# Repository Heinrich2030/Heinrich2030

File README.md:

# Steuer-Rechner

Eigene Web-App zur Schätzung der Einkommensteuer in Deutschland – jahresunabhängig,
läuft komplett im Browser (keine Datenübertragung), mit KI-gestützter Aktualisierung
der Steuerwerte.

## Funktionen
- Einkommensteuer nach § 32a EStG, Grund- und Splittingtarif
- Solidaritätszuschlag (Freigrenze, Milderungszone), Kirchensteuer 8 %/9 %
- Anlage N für 1–2 Personen: Entfernungspauschale, Homeoffice, Arbeitsmittel,
  Arbeitnehmer-Pauschbetrag, Renten- und Basis-Kranken-/Pflegeversicherung
- Kinder: Günstigerprüfung Kindergeld/Kinderfreibetrag, Entlastungsbetrag Alleinerziehende
- Spenden, haushaltsnahe Dienstleistungen und Handwerkerleistungen (§ 35a)
- Anlage KAP: Abgeltungsteuer mit Sparerpauschbetrag
- Erstattung/Nachzahlung im Vergleich zu einbehaltenen Steuern
- Steuerwerte für 2023–2026 (2026 vorläufig); unbekannte Jahre nutzen das neueste Jahr mit Warnhinweis

## Starten
```bash
npm start      # http://localhost:8080
npm test
```
Ohne Build-Schritt – die Dateien können auch direkt auf GitHub Pages oder jedem Webspace liegen.

## Jahresunabhängigkeit & KI-Überwachung
Alle Jahreswerte stehen in `src/data/tax-years.js`, die Rechenlogik in `src/engine/tax.js`
ist jahresneutral. Wie neue Jahre automatisch nachgetragen werden: [docs/KI-UEBERWACHUNG.md](docs/KI-UEBERWACHUNG.md).

## Noch nicht enthalten
Außergewöhnliche Belastungen, Selbständigkeit/Gewerbe, Vermietung, Höchstbeträge der
Vorsorgeaufwendungen, Progressionsvorbehalt, ELSTER-Übermittlung (ERiC).

> Schätzung ohne Gewähr – keine Steuerberatung.

## Spartipps
Die App analysiert deine Eingaben und zeigt Spartipps, sortiert nach Ersparnis in Euro.
Jeder Betrag ist eine echte Vergleichsrechnung mit der Engine („Was wäre, wenn …“), z. B.
Homeoffice-Tage, Handwerkerkosten, Basisrente, Spenden, Splitting-Vorteil, Günstigerprüfung
und Freistellungsauftrag bei Kapitalerträgen. Logik: `src/engine/tipps.js`.

## Weitere Projekte

- [Kabeltester](kabeltester/README.md) – Tischgerät mit 7″-Touchdisplay, 128–256 Testpunkten und 4-Leiter-Widerstandsmessung.

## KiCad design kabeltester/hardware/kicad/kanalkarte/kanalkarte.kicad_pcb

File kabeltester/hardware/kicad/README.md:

# KiCad-Projekte des Kabeltesters

Drei Platinen, erzeugt mit KiCad 7 aus einer gemeinsamen Netzliste (Python-Generator).

| Projekt | Größe | Lagen | Bauteile | Inhalt |
|---|---|---|---|---|
| [`kanalkarte/`](kanalkarte) | 118 × 74 mm | 4 | 413 | 64 Testpunkte, 8× ADG1606, 8× CD74HCT4067, Schutzbeschaltung, DIN-41612-Federleiste. Wird **zweimal** gebaut (Seite A und B). |
| [`messkarte/`](messkarte) | 120 × 90 mm | 4 | 112 | Pico 2, ADS1220, REF5025, Stromsenke, Moduswahl, USB-C, Anschlüsse für Display/Taster/LEDs |
| [`adapter_rj45/`](adapter_rj45) | 100 × 60 mm | 2 | 7 | Vorlage für Steckeradapter: 2× RJ45 + EEPROM, DIN-41612-Messerleiste |

Jedes Projekt enthält Schaltplan (`.kicad_sch`, bei der Kanalkarte mit vier Unterblättern),
Leiterplatte (`.kicad_pcb`), DRC-Bericht und im Ordner `fertigung/`:

- `*-gerber.zip` – Gerber + Bohrdaten (für JLCPCB, Aisler, Multi-CB …)
- `*-bom-jlcpcb.csv` – Stückliste, gruppiert, mit Hersteller-Nummer und (wo bekannt) LCSC-Nummer
- `*-cpl-jlcpcb.csv` – Bestückungsliste (Position, Seite, Drehung)
- `*.step.zip` – 3D-Modell der bestückten Platine

Gehäuse und Gesamtbaugruppe als STEP liegen in [`../../gehaeuse/step/`](../../gehaeuse/step).

## Stand

| Schritt | Status |
|---|---|
| Schaltpläne | fertig; KiCads eigene Netzliste stimmt mit dem Modell überein (automatisch geprüft) |
| Bauteilplatzierung | fertig; keine Überlappungen, Befestigungslöcher passen zu den Gehäusedomen |
| Lagenaufbau | Messkarte 4 Lagen (In1 GND, In2 Signal), Kanalkarte 6 Lagen (In1 GND, In2–In4 Signal), Adapter 2 Lagen; GND-Flächen auf den Außenlagen, 5VA als 0,4-mm-Leiterbahn |
| 3D-Kollisionsprüfung | Platinen, Display, Gehäuse und Boden überschneiden sich nicht |
| **Leiterbahnen** | **offen** – Kanalkarte 944, Messkarte 294, Adapter 21 Verbindungen (siehe unten) |
| Gerber | erzeugt, aber **erst nach dem Routen bestellbar** |

## Vor der Bestellung – Pflichtpunkte

1. **Leiterbahnen ziehen** (Autorouter oder von Hand), dann DRC ohne Fehler.
2. **Pinbelegungen prüfen**, die nicht aus der KiCad-Bibliothek stammen
   (Symbole in `bibliothek/kabeltester.kicad_sym`):
   - ADG1606 (TSSOP-28) – teilweise per Websuche bestätigt (VDD = 1, S16 = 4, S8 = 26, VSS = 27, D = 28),
     der Rest folgt der Pinbelegung der Familie ADG406/1206. Mit dem Datenblatt von Analog Devices abgleichen.
   - BAV199 (SOT-23: 1 = Anode D1, 2 = Kathode D2, 3 = Mitte)
   - PESD2CAN (SOT-23: 1/2 = Leitungen, 3 = gemeinsam)
   - Raspberry Pi Pico 2 (Pinbelegung wie Pico 1)
3. **DIN-41612-Ausrichtung** am ersten Muster prüfen: Messerleiste des Adapters und Federleiste der
   Kanalkarte haben Pin a1 jeweils rechts (von vorne gesehen). Ob Reihe a vorne oder hinten liegt,
   hängt vom Steckverbinder-Hersteller ab – im Zweifel die Federleiste in `layouts.py` um 180° drehen.
4. **LCSC-Nummern** ergänzen: Nur gängige Teile und der ADG1606 (C208204) sind eingetragen. Fehlende
   Nummern im JLCPCB-Teilekatalog zuordnen oder die Teile von Mouser/DigiKey selbst bestücken.
5. Die USB-C-Buchse (Footprint `GCT_USB4105`) hat laut DRC 0,19 mm zwischen Befestigungsloch und Pad
   (Regel 0,25 mm). Das steckt im Standard-Footprint und ist bei JLCPCB fertigbar.

## Leiterbahnen ziehen (Autorouter Freerouting)

In KiCad: *Plugin- und Inhaltsverwaltung* → „Freerouting“ installieren → im Leiterplatten-Editor
*Werkzeuge → Externe Plugins → Freerouting*. Danach *Flächen füllen* (Taste `B`) und *DRC*.

Oder automatisch über den Generator (Java 17+, `Xvfb`, `xdotool` und die Datei `freerouting-1.9.0.jar` von
github.com/freerouting/freerouting nötig):

```bash
FREEROUTING_JAR=/pfad/zu/freerouting-1.9.0.jar python3.12 generator/bauen.py --routen
```

Die Kanalkarte ist sehr dicht (413 Bauteile). Mit 4 Lagen blieben nach dem Autorouter rund 290
Verbindungen offen, deshalb hat sie 6 Lagen. Das Routing läuft in Runden (`generator/routen.py`),
nach jeder Runde wird gespeichert.

## Neu erzeugen

Alles entsteht aus `generator/` – Änderungen dort machen, nicht in den KiCad-Dateien (sie werden
überschrieben). Voraussetzung: KiCad 7 mit Python-Modul `pcbnew` (Linux: Paket `kicad`, dazu
`kicad-symbols`, `kicad-footprints`, `kicad-packages3d`).

```bash
cd kabeltester/hardware/kicad
python3.12 generator/bauen.py              # Schaltpläne, Leiterplatten, Fertigungsdaten
python3.12 generator/bauen.py --nur-schaltplan
```

| Datei | Aufgabe |
|---|---|
| `generator/platinen.py` | Netzlisten aller Platinen (Bauteile, Werte, Footprints, Netze) |
| `generator/layouts.py` | Platzierung und Mechanik (Maße, Lochpositionen) |
| `generator/schaltplan.py` | schreibt die `.kicad_sch`-Dateien |
| `generator/leiterplatte.py` | baut die `.kicad_pcb`, Flächen, DRC, Fertigungsdaten |
| `generator/netzvergleich.py` | vergleicht KiCads Netzliste mit dem Modell |
| `generator/eigene_bibliothek.py` | eigene Symbole und den Pico-2-Footprint |

## Gehäuse als STEP

```bash
pip install cadquery
python ../../gehaeuse/gehaeuse_step.py
```

Erzeugt `gehaeuse_oberschale.step/.stl`, `gehaeuse_boden.step/.stl` und die Gesamtbaugruppe
`kabeltester_baugruppe.step.zip` (gezippt ca. 40 MB, entpackt ca. 290 MB). STEP lässt sich in
SolidWorks, Fusion 360, FreeCAD, Onshape und den meisten anderen CAD-Programmen öffnen.

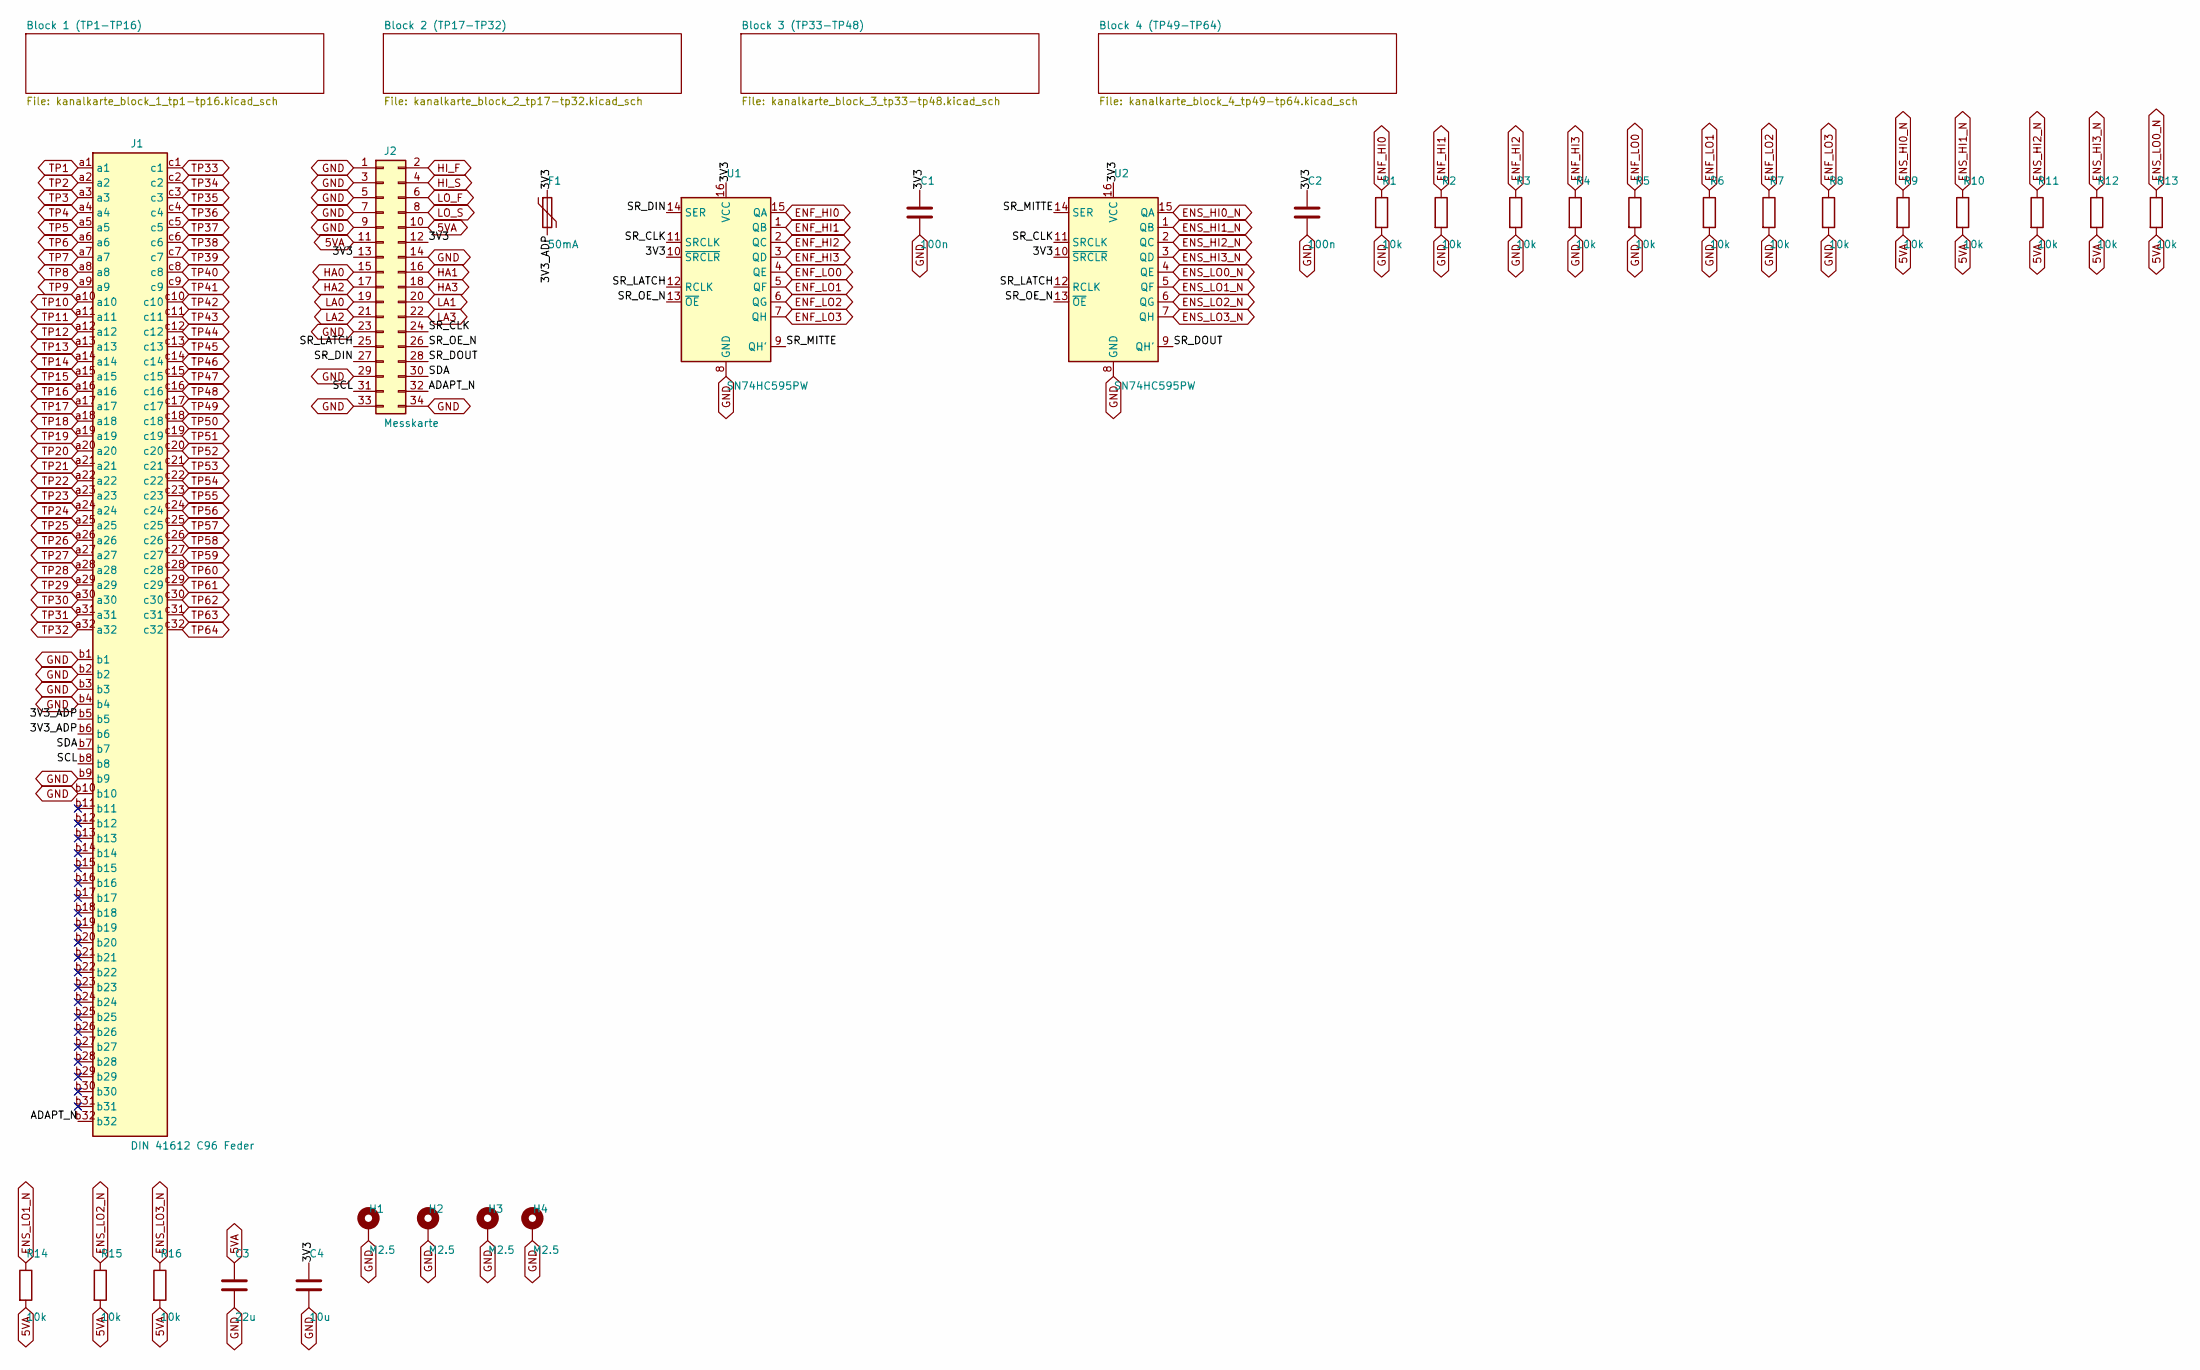
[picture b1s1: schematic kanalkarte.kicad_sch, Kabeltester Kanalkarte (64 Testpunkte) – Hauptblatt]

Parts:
C1, C2: 100n; C_0603_1608Metric; LCSC C14663
C3: 22u; C_1206_3216Metric
C4: 10u; C_0805_2012Metric; LCSC C15850
F1: 50mA; Fuse_0805_2012Metric; MPN Bourns MF-PSMF005X-2
H1, H2, H3, H4: M2.5; MountingHole_2.7mm_M2.5_Pad_Via
J1: DIN 41612 C96 Feder; DIN41612_C_3x32_Female_Vertical_THT; MPN Harting DIN-Signal C096 F gerade
J2: Messkarte; IDC-Header_2x17_P2.54mm_Vertical; MPN Wannenstecker 2x17
R1, R2, R3, R4, R5, R6, R7, R8, R9, R10, R11, R12, R13, R14, R15, R16: 10k; R_0603_1608Metric; LCSC C25804
U1, U2: SN74HC595PW; TSSOP-16_4.4x5mm_P0.65mm; LCSC C5947

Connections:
3V3: C1.1, C2.1, C4.1, F1.1, J2.12, J2.13, U1.10 (~SRCLR), U1.16 (VCC), U2.10 (~SRCLR), U2.16 (VCC)
3V3_ADP: F1.2, J1.b5, J1.b6
5VA: C3.1, J2.10, J2.11, R9.2, R10.2, R11.2, R12.2, R13.2, R14.2, R15.2, R16.2; also elsewhere on the board
ADAPT_N: J1.b32, J2.32
ENF_HI0: R1.1, U1.15 (QA); also elsewhere on the board
ENF_HI1: R2.1, U1.1 (QB); also elsewhere on the board
ENF_HI2: R3.1, U1.2 (QC); also elsewhere on the board
ENF_HI3: R4.1, U1.3 (QD); also elsewhere on the board
ENF_LO0: R5.1, U1.4 (QE); also elsewhere on the board
ENF_LO1: R6.1, U1.5 (QF); also elsewhere on the board
ENF_LO2: R7.1, U1.6 (QG); also elsewhere on the board
ENF_LO3: R8.1, U1.7 (QH); also elsewhere on the board
ENS_HI0_N: R9.1, U2.15 (QA); also elsewhere on the board
ENS_HI1_N: R10.1, U2.1 (QB); also elsewhere on the board
ENS_HI2_N: R11.1, U2.2 (QC); also elsewhere on the board
ENS_HI3_N: R12.1, U2.3 (QD); also elsewhere on the board
ENS_LO0_N: R13.1, U2.4 (QE); also elsewhere on the board
ENS_LO1_N: R14.1, U2.5 (QF); also elsewhere on the board
ENS_LO2_N: R15.1, U2.6 (QG); also elsewhere on the board
ENS_LO3_N: R16.1, U2.7 (QH); also elsewhere on the board
GND: C1.2, C2.2, C3.2, C4.2, H1.1, H2.1, H3.1, H4.1, J1.b1, J1.b2, J1.b3, J1.b4, J1.b9, J1.b10, J2.1, J2.3, J2.5, J2.7, J2.9, J2.14, J2.23, J2.29, J2.33, J2.34, R1.2, R2.2, R3.2, R4.2, R5.2, R6.2, R7.2, R8.2, U1.8 (GND), U2.8 (GND); also elsewhere on the board
HA0: J2.15; also elsewhere on the board
HA1: J2.16; also elsewhere on the board
HA2: J2.17; also elsewhere on the board
HA3: J2.18; also elsewhere on the board
HI_F: J2.2; also elsewhere on the board
HI_S: J2.4; also elsewhere on the board
LA0: J2.19; also elsewhere on the board
LA1: J2.20; also elsewhere on the board
LA2: J2.21; also elsewhere on the board
LA3: J2.22; also elsewhere on the board
LO_F: J2.6; also elsewhere on the board
LO_S: J2.8; also elsewhere on the board
SCL: J1.b8, J2.31
SDA: J1.b7, J2.30
SR_CLK: J2.24, U1.11 (SRCLK), U2.11 (SRCLK)
SR_DIN: J2.27, U1.14 (SER)
SR_DOUT: J2.28, U2.9 (QH')
SR_LATCH: J2.25, U1.12 (RCLK), U2.12 (RCLK)
SR_MITTE: U1.9 (QH'), U2.14 (SER)
SR_OE_N: J2.26, U1.13 (~OE), U2.13 (~OE)
TP1: J1.a1; also elsewhere on the board
TP2: J1.a2; also elsewhere on the board
TP3: J1.a3; also elsewhere on the board
TP4: J1.a4; also elsewhere on the board
TP5: J1.a5; also elsewhere on the board
TP6: J1.a6; also elsewhere on the board
TP7: J1.a7; also elsewhere on the board
TP8: J1.a8; also elsewhere on the board
TP9: J1.a9; also elsewhere on the board
TP10: J1.a10; also elsewhere on the board
TP11: J1.a11; also elsewhere on the board
TP12: J1.a12; also elsewhere on the board
TP13: J1.a13; also elsewhere on the board
TP14: J1.a14; also elsewhere on the board
TP15: J1.a15; also elsewhere on the board
TP16: J1.a16; also elsewhere on the board
TP17: J1.a17; also elsewhere on the board
TP18: J1.a18; also elsewhere on the board
TP19: J1.a19; also elsewhere on the board
TP20: J1.a20; also elsewhere on the board
TP21: J1.a21; also elsewhere on the board
TP22: J1.a22; also elsewhere on the board
TP23: J1.a23; also elsewhere on the board
TP24: J1.a24; also elsewhere on the board
TP25: J1.a25; also elsewhere on the board
TP26: J1.a26; also elsewhere on the board
TP27: J1.a27; also elsewhere on the board
TP28: J1.a28; also elsewhere on the board
TP29: J1.a29; also elsewhere on the board
TP30: J1.a30; also elsewhere on the board
TP31: J1.a31; also elsewhere on the board
TP32: J1.a32; also elsewhere on the board
TP33: J1.c1; also elsewhere on the board
TP34: J1.c2; also elsewhere on the board
TP35: J1.c3; also elsewhere on the board
TP36: J1.c4; also elsewhere on the board
TP37: J1.c5; also elsewhere on the board
TP38: J1.c6; also elsewhere on the board
TP39: J1.c7; also elsewhere on the board
TP40: J1.c8; also elsewhere on the board
TP41: J1.c9; also elsewhere on the board
TP42: J1.c10; also elsewhere on the board
TP43: J1.c11; also elsewhere on the board
TP44: J1.c12; also elsewhere on the board
TP45: J1.c13; also elsewhere on the board
TP46: J1.c14; also elsewhere on the board
TP47: J1.c15; also elsewhere on the board
TP48: J1.c16; also elsewhere on the board
TP49: J1.c17; also elsewhere on the board
TP50: J1.c18; also elsewhere on the board
TP51: J1.c19; also elsewhere on the board
TP52: J1.c20; also elsewhere on the board
TP53: J1.c21; also elsewhere on the board
TP54: J1.c22; also elsewhere on the board
TP55: J1.c23; also elsewhere on the board
TP56: J1.c24; also elsewhere on the board
TP57: J1.c25; also elsewhere on the board
TP58: J1.c26; also elsewhere on the board
TP59: J1.c27; also elsewhere on the board
TP60: J1.c28; also elsewhere on the board
TP61: J1.c29; also elsewhere on the board
TP62: J1.c30; also elsewhere on the board
TP63: J1.c31; also elsewhere on the board
TP64: J1.c32; also elsewhere on the board

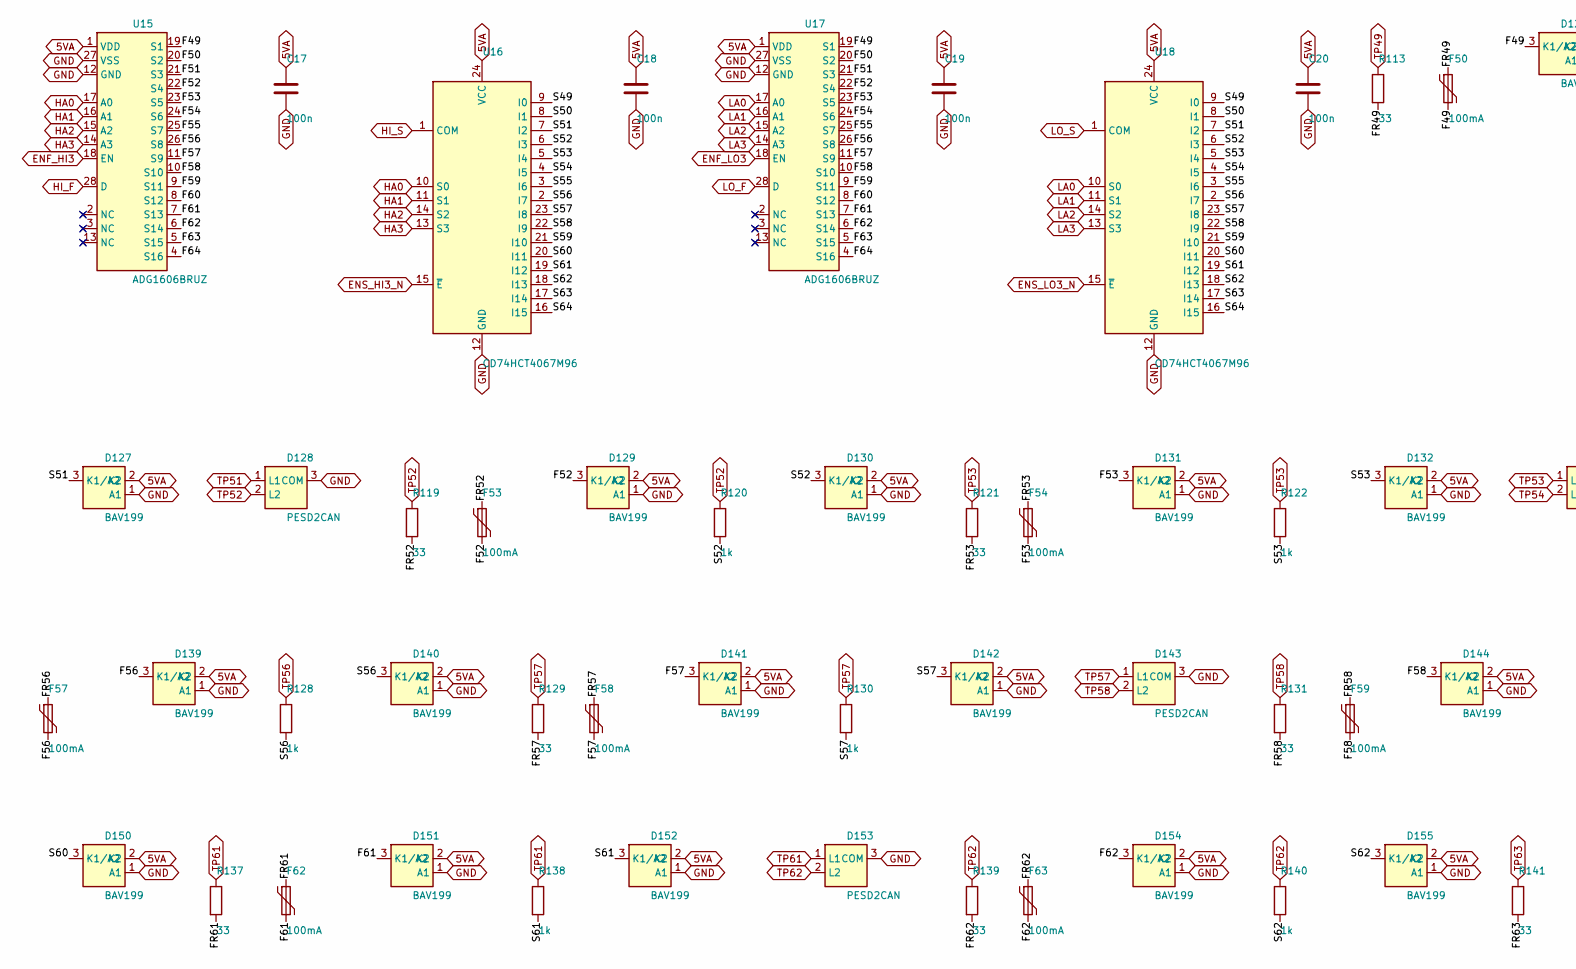
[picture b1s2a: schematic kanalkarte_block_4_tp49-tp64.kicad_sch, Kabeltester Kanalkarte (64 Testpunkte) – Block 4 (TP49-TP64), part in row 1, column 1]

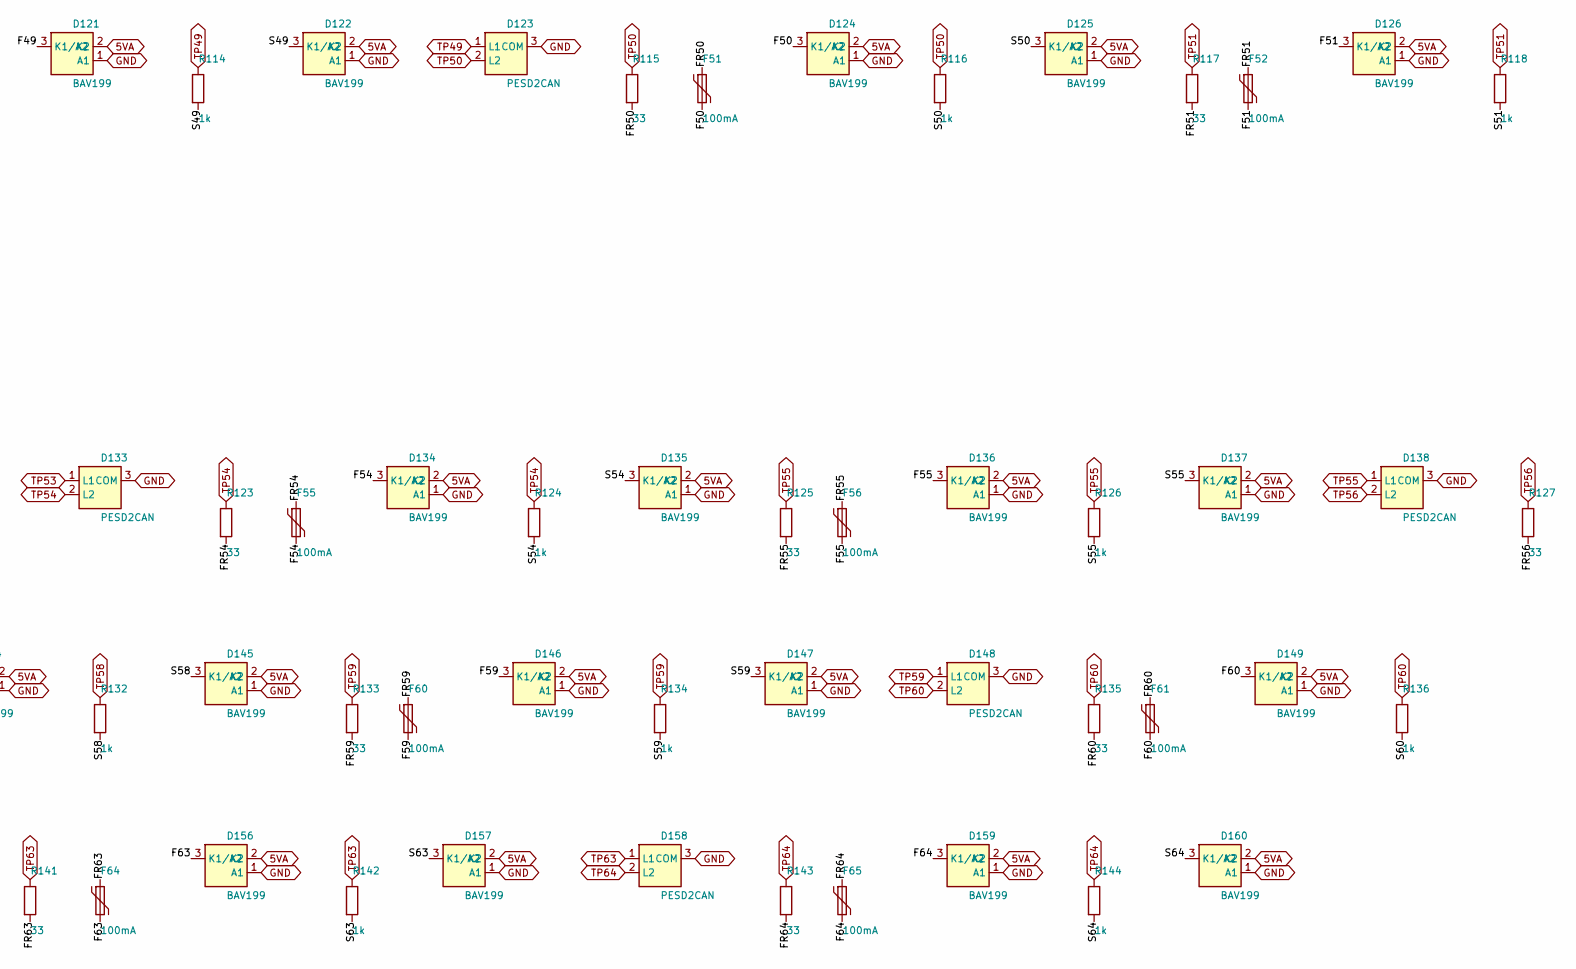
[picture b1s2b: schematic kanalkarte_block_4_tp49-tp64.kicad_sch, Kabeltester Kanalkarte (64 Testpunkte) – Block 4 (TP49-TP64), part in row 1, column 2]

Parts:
C17, C18, C19, C20: 100n; C_0603_1608Metric; LCSC C14663
D121, D122, D124, D125, D126, D127, D129, D130, D131, D132, D134, D135, D136, D137, D139, D140, D141, D142, D144, D145, D146, D147, D149, D150, D151, D152, D154, D155, D156, D157, D159, D160: BAV199; SOT-23
D123, D128, D133, D138, D143, D148, D153, D158: PESD2CAN; SOT-23
F50, F51, F52, F53, F54, F55, F56, F57, F58, F59, F60, F61, F62, F63, F64, F65: 100mA; Fuse_1206_3216Metric; MPN Bourns MF-USMF010-2
R113, R115, R117, R119, R121, R123, R125, R127, R129, R131, R133, R135, R137, R139, R141, R143: 33; R_1206_3216Metric; MPN CRCW120633R0FKEAHP
R114, R116, R118, R120, R122, R124, R126, R128, R130, R132, R134, R136, R138, R140, R142, R144: 1k; R_0603_1608Metric; LCSC C21190
U15, U17: ADG1606BRUZ; TSSOP-28_4.4x9.7mm_P0.65mm; LCSC C208204
U16, U18: CD74HCT4067M96; SOIC-24W_7.5x15.4mm_P1.27mm

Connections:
5VA: C17.1, C18.1, C19.1, C20.1, D121.2 (K2), D122.2 (K2), D124.2 (K2), D125.2 (K2), D126.2 (K2), D127.2 (K2), D129.2 (K2), D130.2 (K2), D131.2 (K2), D132.2 (K2), D134.2 (K2), D135.2 (K2), D136.2 (K2), D137.2 (K2), D139.2 (K2), D140.2 (K2), D141.2 (K2), D142.2 (K2), D144.2 (K2), D145.2 (K2), D146.2 (K2), D147.2 (K2), D149.2 (K2), D150.2 (K2), D151.2 (K2), D152.2 (K2), D154.2 (K2), D155.2 (K2), D156.2 (K2), D157.2 (K2), D159.2 (K2), D160.2 (K2), U15.1 (VDD), U16.24 (VCC), U17.1 (VDD), U18.24 (VCC); also elsewhere on the board
ENF_HI3: U15.18 (EN); also elsewhere on the board
ENF_LO3: U17.18 (EN); also elsewhere on the board
ENS_HI3_N: U16.15 (~E); also elsewhere on the board
ENS_LO3_N: U18.15 (~E); also elsewhere on the board
F49: D121.3 (K1/A2), F50.2, U15.19 (S1), U17.19 (S1)
F50: D124.3 (K1/A2), F51.2, U15.20 (S2), U17.20 (S2)
F51: D126.3 (K1/A2), F52.2, U15.21 (S3), U17.21 (S3)
F52: D129.3 (K1/A2), F53.2, U15.22 (S4), U17.22 (S4)
F53: D131.3 (K1/A2), F54.2, U15.23 (S5), U17.23 (S5)
F54: D134.3 (K1/A2), F55.2, U15.24 (S6), U17.24 (S6)
F55: D136.3 (K1/A2), F56.2, U15.25 (S7), U17.25 (S7)
F56: D139.3 (K1/A2), F57.2, U15.26 (S8), U17.26 (S8)
F57: D141.3 (K1/A2), F58.2, U15.11 (S9), U17.11 (S9)
F58: D144.3 (K1/A2), F59.2, U15.10 (S10), U17.10 (S10)
F59: D146.3 (K1/A2), F60.2, U15.9 (S11), U17.9 (S11)
F60: D149.3 (K1/A2), F61.2, U15.8 (S12), U17.8 (S12)
F61: D151.3 (K1/A2), F62.2, U15.7 (S13), U17.7 (S13)
F62: D154.3 (K1/A2), F63.2, U15.6 (S14), U17.6 (S14)
F63: D156.3 (K1/A2), F64.2, U15.5 (S15), U17.5 (S15)
F64: D159.3 (K1/A2), F65.2, U15.4 (S16), U17.4 (S16)
FR49: F50.1, R113.2
FR50: F51.1, R115.2
FR51: F52.1, R117.2
FR52: F53.1, R119.2
FR53: F54.1, R121.2
FR54: F55.1, R123.2
FR55: F56.1, R125.2
FR56: F57.1, R127.2
FR57: F58.1, R129.2
FR58: F59.1, R131.2
FR59: F60.1, R133.2
FR60: F61.1, R135.2
FR61: F62.1, R137.2
FR62: F63.1, R139.2
FR63: F64.1, R141.2
FR64: F65.1, R143.2
GND: C17.2, C18.2, C19.2, C20.2, D121.1 (A1), D122.1 (A1), D123.3 (COM), D124.1 (A1), D125.1 (A1), D126.1 (A1), D127.1 (A1), D128.3 (COM), D129.1 (A1), D130.1 (A1), D131.1 (A1), D132.1 (A1), D133.3 (COM), D134.1 (A1), D135.1 (A1), D136.1 (A1), D137.1 (A1), D138.3 (COM), D139.1 (A1), D140.1 (A1), D141.1 (A1), D142.1 (A1), D143.3 (COM), D144.1 (A1), D145.1 (A1), D146.1 (A1), D147.1 (A1), D148.3 (COM), D149.1 (A1), D150.1 (A1), D151.1 (A1), D152.1 (A1), D153.3 (COM), D154.1 (A1), D155.1 (A1), D156.1 (A1), D157.1 (A1), D158.3 (COM), D159.1 (A1), D160.1 (A1), U15.12 (GND), U15.27 (VSS), U16.12 (GND), U17.12 (GND), U17.27 (VSS), U18.12 (GND); also elsewhere on the board
HA0: U15.17 (A0), U16.10 (S0); also elsewhere on the board
HA1: U15.16 (A1), U16.11 (S1); also elsewhere on the board
HA2: U15.15 (A2), U16.14 (S2); also elsewhere on the board
HA3: U15.14 (A3), U16.13 (S3); also elsewhere on the board
HI_F: U15.28 (D); also elsewhere on the board
HI_S: U16.1 (COM); also elsewhere on the board
LA0: U17.17 (A0), U18.10 (S0); also elsewhere on the board
LA1: U17.16 (A1), U18.11 (S1); also elsewhere on the board
LA2: U17.15 (A2), U18.14 (S2); also elsewhere on the board
LA3: U17.14 (A3), U18.13 (S3); also elsewhere on the board
LO_F: U17.28 (D); also elsewhere on the board
LO_S: U18.1 (COM); also elsewhere on the board
S49: D122.3 (K1/A2), R114.2, U16.9 (I0), U18.9 (I0)
S50: D125.3 (K1/A2), R116.2, U16.8 (I1), U18.8 (I1)
S51: D127.3 (K1/A2), R118.2, U16.7 (I2), U18.7 (I2)
S52: D130.3 (K1/A2), R120.2, U16.6 (I3), U18.6 (I3)
S53: D132.3 (K1/A2), R122.2, U16.5 (I4), U18.5 (I4)
S54: D135.3 (K1/A2), R124.2, U16.4 (I5), U18.4 (I5)
S55: D137.3 (K1/A2), R126.2, U16.3 (I6), U18.3 (I6)
S56: D140.3 (K1/A2), R128.2, U16.2 (I7), U18.2 (I7)
S57: D142.3 (K1/A2), R130.2, U16.23 (I8), U18.23 (I8)
S58: D145.3 (K1/A2), R132.2, U16.22 (I9), U18.22 (I9)
S59: D147.3 (K1/A2), R134.2, U16.21 (I10), U18.21 (I10)
S60: D150.3 (K1/A2), R136.2, U16.20 (I11), U18.20 (I11)
S61: D152.3 (K1/A2), R138.2, U16.19 (I12), U18.19 (I12)
S62: D155.3 (K1/A2), R140.2, U16.18 (I13), U18.18 (I13)
S63: D157.3 (K1/A2), R142.2, U16.17 (I14), U18.17 (I14)
S64: D160.3 (K1/A2), R144.2, U16.16 (I15), U18.16 (I15)
TP49: D123.1 (L1), R113.1, R114.1; also elsewhere on the board
TP50: D123.2 (L2), R115.1, R116.1; also elsewhere on the board
TP51: D128.1 (L1), R117.1, R118.1; also elsewhere on the board
TP52: D128.2 (L2), R119.1, R120.1; also elsewhere on the board
TP53: D133.1 (L1), R121.1, R122.1; also elsewhere on the board
TP54: D133.2 (L2), R123.1, R124.1; also elsewhere on the board
TP55: D138.1 (L1), R125.1, R126.1; also elsewhere on the board
TP56: D138.2 (L2), R127.1, R128.1; also elsewhere on the board
TP57: D143.1 (L1), R129.1, R130.1; also elsewhere on the board
TP58: D143.2 (L2), R131.1, R132.1; also elsewhere on the board
TP59: D148.1 (L1), R133.1, R134.1; also elsewhere on the board
TP60: D148.2 (L2), R135.1, R136.1; also elsewhere on the board
TP61: D153.1 (L1), R137.1, R138.1; also elsewhere on the board
TP62: D153.2 (L2), R139.1, R140.1; also elsewhere on the board
TP63: D158.1 (L1), R141.1, R142.1; also elsewhere on the board
TP64: D158.2 (L2), R143.1, R144.1; also elsewhere on the board

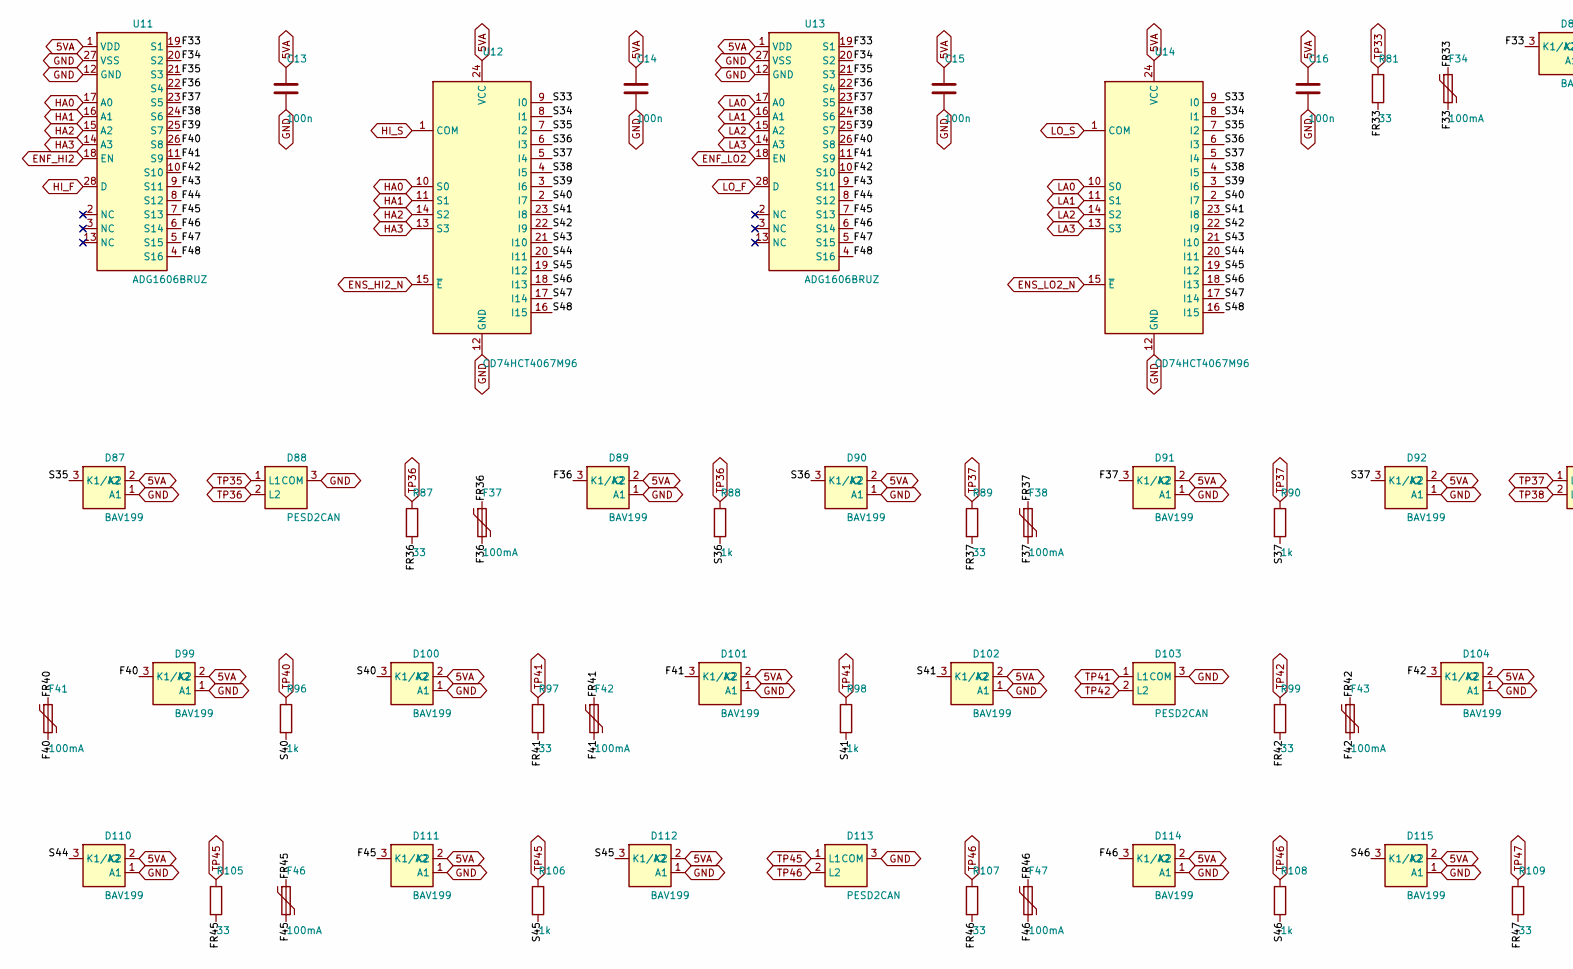
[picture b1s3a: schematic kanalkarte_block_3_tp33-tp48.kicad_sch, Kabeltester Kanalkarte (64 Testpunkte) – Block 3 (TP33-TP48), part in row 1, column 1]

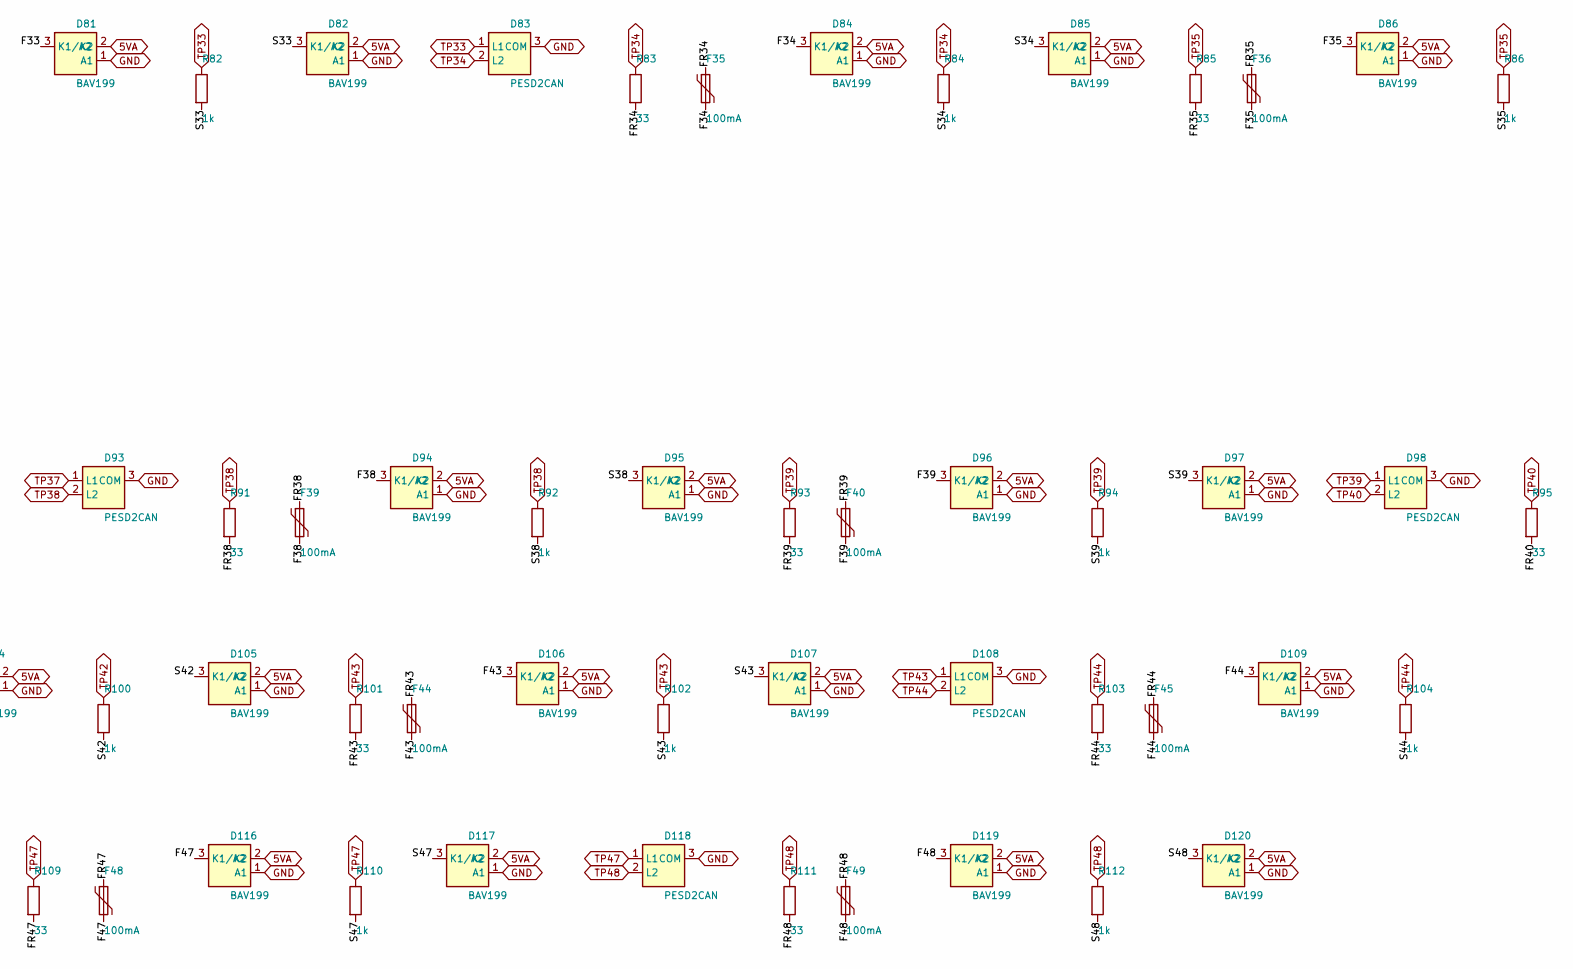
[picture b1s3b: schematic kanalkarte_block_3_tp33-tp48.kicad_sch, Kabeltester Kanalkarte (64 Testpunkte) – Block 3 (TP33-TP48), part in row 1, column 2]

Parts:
C13, C14, C15, C16: 100n; C_0603_1608Metric; LCSC C14663
D81, D82, D84, D85, D86, D87, D89, D90, D91, D92, D94, D95, D96, D97, D99, D100, D101, D102, D104, D105, D106, D107, D109, D110, D111, D112, D114, D115, D116, D117, D119, D120: BAV199; SOT-23
D83, D88, D93, D98, D103, D108, D113, D118: PESD2CAN; SOT-23
F34, F35, F36, F37, F38, F39, F40, F41, F42, F43, F44, F45, F46, F47, F48, F49: 100mA; Fuse_1206_3216Metric; MPN Bourns MF-USMF010-2
R81, R83, R85, R87, R89, R91, R93, R95, R97, R99, R101, R103, R105, R107, R109, R111: 33; R_1206_3216Metric; MPN CRCW120633R0FKEAHP
R82, R84, R86, R88, R90, R92, R94, R96, R98, R100, R102, R104, R106, R108, R110, R112: 1k; R_0603_1608Metric; LCSC C21190
U11, U13: ADG1606BRUZ; TSSOP-28_4.4x9.7mm_P0.65mm; LCSC C208204
U12, U14: CD74HCT4067M96; SOIC-24W_7.5x15.4mm_P1.27mm

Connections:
5VA: C13.1, C14.1, C15.1, C16.1, D81.2 (K2), D82.2 (K2), D84.2 (K2), D85.2 (K2), D86.2 (K2), D87.2 (K2), D89.2 (K2), D90.2 (K2), D91.2 (K2), D92.2 (K2), D94.2 (K2), D95.2 (K2), D96.2 (K2), D97.2 (K2), D99.2 (K2), D100.2 (K2), D101.2 (K2), D102.2 (K2), D104.2 (K2), D105.2 (K2), D106.2 (K2), D107.2 (K2), D109.2 (K2), D110.2 (K2), D111.2 (K2), D112.2 (K2), D114.2 (K2), D115.2 (K2), D116.2 (K2), D117.2 (K2), D119.2 (K2), D120.2 (K2), U11.1 (VDD), U12.24 (VCC), U13.1 (VDD), U14.24 (VCC); also elsewhere on the board
ENF_HI2: U11.18 (EN); also elsewhere on the board
ENF_LO2: U13.18 (EN); also elsewhere on the board
ENS_HI2_N: U12.15 (~E); also elsewhere on the board
ENS_LO2_N: U14.15 (~E); also elsewhere on the board
F33: D81.3 (K1/A2), F34.2, U11.19 (S1), U13.19 (S1)
F34: D84.3 (K1/A2), F35.2, U11.20 (S2), U13.20 (S2)
F35: D86.3 (K1/A2), F36.2, U11.21 (S3), U13.21 (S3)
F36: D89.3 (K1/A2), F37.2, U11.22 (S4), U13.22 (S4)
F37: D91.3 (K1/A2), F38.2, U11.23 (S5), U13.23 (S5)
F38: D94.3 (K1/A2), F39.2, U11.24 (S6), U13.24 (S6)
F39: D96.3 (K1/A2), F40.2, U11.25 (S7), U13.25 (S7)
F40: D99.3 (K1/A2), F41.2, U11.26 (S8), U13.26 (S8)
F41: D101.3 (K1/A2), F42.2, U11.11 (S9), U13.11 (S9)
F42: D104.3 (K1/A2), F43.2, U11.10 (S10), U13.10 (S10)
F43: D106.3 (K1/A2), F44.2, U11.9 (S11), U13.9 (S11)
F44: D109.3 (K1/A2), F45.2, U11.8 (S12), U13.8 (S12)
F45: D111.3 (K1/A2), F46.2, U11.7 (S13), U13.7 (S13)
F46: D114.3 (K1/A2), F47.2, U11.6 (S14), U13.6 (S14)
F47: D116.3 (K1/A2), F48.2, U11.5 (S15), U13.5 (S15)
F48: D119.3 (K1/A2), F49.2, U11.4 (S16), U13.4 (S16)
FR33: F34.1, R81.2
FR34: F35.1, R83.2
FR35: F36.1, R85.2
FR36: F37.1, R87.2
FR37: F38.1, R89.2
FR38: F39.1, R91.2
FR39: F40.1, R93.2
FR40: F41.1, R95.2
FR41: F42.1, R97.2
FR42: F43.1, R99.2
FR43: F44.1, R101.2
FR44: F45.1, R103.2
FR45: F46.1, R105.2
FR46: F47.1, R107.2
FR47: F48.1, R109.2
FR48: F49.1, R111.2
GND: C13.2, C14.2, C15.2, C16.2, D81.1 (A1), D82.1 (A1), D83.3 (COM), D84.1 (A1), D85.1 (A1), D86.1 (A1), D87.1 (A1), D88.3 (COM), D89.1 (A1), D90.1 (A1), D91.1 (A1), D92.1 (A1), D93.3 (COM), D94.1 (A1), D95.1 (A1), D96.1 (A1), D97.1 (A1), D98.3 (COM), D99.1 (A1), D100.1 (A1), D101.1 (A1), D102.1 (A1), D103.3 (COM), D104.1 (A1), D105.1 (A1), D106.1 (A1), D107.1 (A1), D108.3 (COM), D109.1 (A1), D110.1 (A1), D111.1 (A1), D112.1 (A1), D113.3 (COM), D114.1 (A1), D115.1 (A1), D116.1 (A1), D117.1 (A1), D118.3 (COM), D119.1 (A1), D120.1 (A1), U11.12 (GND), U11.27 (VSS), U12.12 (GND), U13.12 (GND), U13.27 (VSS), U14.12 (GND); also elsewhere on the board
HA0: U11.17 (A0), U12.10 (S0); also elsewhere on the board
HA1: U11.16 (A1), U12.11 (S1); also elsewhere on the board
HA2: U11.15 (A2), U12.14 (S2); also elsewhere on the board
HA3: U11.14 (A3), U12.13 (S3); also elsewhere on the board
HI_F: U11.28 (D); also elsewhere on the board
HI_S: U12.1 (COM); also elsewhere on the board
LA0: U13.17 (A0), U14.10 (S0); also elsewhere on the board
LA1: U13.16 (A1), U14.11 (S1); also elsewhere on the board
LA2: U13.15 (A2), U14.14 (S2); also elsewhere on the board
LA3: U13.14 (A3), U14.13 (S3); also elsewhere on the board
LO_F: U13.28 (D); also elsewhere on the board
LO_S: U14.1 (COM); also elsewhere on the board
S33: D82.3 (K1/A2), R82.2, U12.9 (I0), U14.9 (I0)
S34: D85.3 (K1/A2), R84.2, U12.8 (I1), U14.8 (I1)
S35: D87.3 (K1/A2), R86.2, U12.7 (I2), U14.7 (I2)
S36: D90.3 (K1/A2), R88.2, U12.6 (I3), U14.6 (I3)
S37: D92.3 (K1/A2), R90.2, U12.5 (I4), U14.5 (I4)
S38: D95.3 (K1/A2), R92.2, U12.4 (I5), U14.4 (I5)
S39: D97.3 (K1/A2), R94.2, U12.3 (I6), U14.3 (I6)
S40: D100.3 (K1/A2), R96.2, U12.2 (I7), U14.2 (I7)
S41: D102.3 (K1/A2), R98.2, U12.23 (I8), U14.23 (I8)
S42: D105.3 (K1/A2), R100.2, U12.22 (I9), U14.22 (I9)
S43: D107.3 (K1/A2), R102.2, U12.21 (I10), U14.21 (I10)
S44: D110.3 (K1/A2), R104.2, U12.20 (I11), U14.20 (I11)
S45: D112.3 (K1/A2), R106.2, U12.19 (I12), U14.19 (I12)
S46: D115.3 (K1/A2), R108.2, U12.18 (I13), U14.18 (I13)
S47: D117.3 (K1/A2), R110.2, U12.17 (I14), U14.17 (I14)
S48: D120.3 (K1/A2), R112.2, U12.16 (I15), U14.16 (I15)
TP33: D83.1 (L1), R81.1, R82.1; also elsewhere on the board
TP34: D83.2 (L2), R83.1, R84.1; also elsewhere on the board
TP35: D88.1 (L1), R85.1, R86.1; also elsewhere on the board
TP36: D88.2 (L2), R87.1, R88.1; also elsewhere on the board
TP37: D93.1 (L1), R89.1, R90.1; also elsewhere on the board
TP38: D93.2 (L2), R91.1, R92.1; also elsewhere on the board
TP39: D98.1 (L1), R93.1, R94.1; also elsewhere on the board
TP40: D98.2 (L2), R95.1, R96.1; also elsewhere on the board
TP41: D103.1 (L1), R97.1, R98.1; also elsewhere on the board
TP42: D103.2 (L2), R99.1, R100.1; also elsewhere on the board
TP43: D108.1 (L1), R101.1, R102.1; also elsewhere on the board
TP44: D108.2 (L2), R103.1, R104.1; also elsewhere on the board
TP45: D113.1 (L1), R105.1, R106.1; also elsewhere on the board
TP46: D113.2 (L2), R107.1, R108.1; also elsewhere on the board
TP47: D118.1 (L1), R109.1, R110.1; also elsewhere on the board
TP48: D118.2 (L2), R111.1, R112.1; also elsewhere on the board
